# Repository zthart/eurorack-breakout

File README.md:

# Eurorack Power Breakout

**Warning**: I am, perhaps, the furthest thing there is from an EE or CE. 
I have a rudimentary (at best) understanding of the physics involved in the electronics.
I mostly understand the following:

1. Give black rectangles too much power and \*pop\*.
2. Give spicy cylinders too much power and \*pop\*.
3. Send power the wrong way and something very expensive goes \*pop\*.
4. \*pop\* is bad.

The `eurorack_breakout` directory contains the KiCad project, schematic, and pcb files for this project.

The first prototypes of the `norev` boards have performed well at what they're meant to do, and a new batch of the boards has been ordered with a few improvements (reverse-polarity protection diodes for the rack supply +12/-12/+5V rails, primarily).
I have some extras of both the `norev` and `rev0.3` boards, and would be happy to send you one if you reach out and cover shipping.

## Oops! All SMD

You'll notice everything is a SMD component, aside from the pin headers on either end of the PCB.
None of the package sizes are _too_ too difficult, so I'm confident you'll figure it out.
The two ceramic decoupling capacitors on the linear regulators (`C3` and `C6`), as well as the reverse polarity diodes (`D1-D3`) are the smallest packages, and may be tricky.
Just be patient use tweezers, flux, and make sure your soldering iron is tinned and you're using a relatively-small-ish conical tip.
I used the hand-soldering extended footprints KiCad provides for each package when possible, so every component should have enough room to get a soldering iron around.

## Optional Regulated Power

As is, the board (when populated with only the reverse-polarity protection diodes) can be used to route 10- or 16-pin Eurorack power from a 2-by connector to a 1-by connector with one less ground. 
The Gate and CV lines on the 16-pin connector are also not routed anywhere (except between columns).
If you need these lines my recommendation is to simply not need them (I don't need them for my purposes so I decided not to route them, I don't know how many modules actually use them).
There are two solder jumpers on the board -- `JP1` and `JP2` -- to pass +12V from the Eurorack power through the LM1117-3.3 and LM1117-5.0 circuits, respectively.
If you're using 5V tolerant digital circuitry in your module and want to support just 16-pin connectors, you don't even need to populate the board (sans diodes - those need to be populated for anything but ground be connected).

### Messing up

If you mess up, both halves of the circuit are identical (sans ferrite bead).
The silkscreen will be wrong, but there's not much stopping you from using the 3V3 side as the 5V side or vice-versa.
This might be helpful if you make a mistake while soldering.
If you have soldered some components on successfully before your mistake, I'd recommend cutting the jumper trace that corresponds to the circuit on which you've made your mistake.

### 3V3 Circuit

The 3.3V circuit consists of the following:

|Part Ref|Value|Type|
|:-:|--:|--:|
|`U1`|LM1117-3.3|Linear Regulator|
|`C1`|47uF|Aluminum Polymer Cap|
|`C2`|47uF|Aluminum Polymer Cap|
|`C3`|0.1uF|Ceramic Cap|
|`FB1`\*| -- |Ferrite Bead|

_\*The ferrite bead is not needed if you don't want/need a slightly cleaner 3.3V supply._
_The circuit will work without it populated, but pin 7 on the breakout-side connector will be NC. You can bridge the FB footprint, or pin 7 and 8 on the breakout-side connector directly if you would like 2 3V3 pins._

If you don't need 3.3V power for your testing, cut the trace connecting the two halves of the jumper with a razor blade or hobby knife (carefully).
You can also not cut it, and just leave the entire portion of the board unpopulated.
Note that the Aluminum caps are polarized - the footprints and packaging should make it clear which side is which. 
All 4 caps have the same orientation.

### 5V Circuit

The 5V circuit consists of the following:

|Part Ref|Value|Type|
|:-:|--:|--:|
|`U2`|LM1117-5.0|Linear Regulator|
|`C4`|47uF|Aluminum Polymer Cap|
|`C5`|47uF|Aluminum Polymer Cap|
|`C6`|0.1uf|Ceramic Cap|

If you don't need 5V power for your testing, cut the trace connecting the two halves of the jumper with a razor blade or hobby knife (carefully).
The same applies to the 3V3 circuit - you can choose to not cut it as well. 
If the circuit is unpopulated nothing will change.
I would personally recommend cutting it only in the case that you mess up one half of it and still want to use the other.

## BOM

|Part Ref|Value|Type|Link|
|:-:|--:|--:|:-:|
|`C1`, `C2`, `C4`, `C5`|47uF|Aluminum Polymer Cap|([digikey](https://www.digikey.com/en/products/detail/kemet/A768EB476M1VLAE042/13420538))|
|`C3`, `C6`|0.1uF|Ceramic Cap|([digikey](https://www.digikey.com/en/products/detail/w-rth-elektronik/885012208087/5454754))|
|`U1`|LM1117-3.3\*|Linear Regulator|([digikey](https://www.digikey.com/en/products/detail/on-semiconductor/LM1117MPX-33NOPB/13559953))|
|`U2`|LM1117-5.0\*|Linear Regulator|([digikey](https://www.digikey.com/en/products/detail/on-semiconductor/LM1117MPX-50NOPB/13559966))|
|`FB1`| -- |Ferrite Bead|([digikey](https://www.digikey.com/en/products/detail/w-rth-elektronik/742792312/1639577))|
|`D1-D3`|1N5819\*\*|Schottky Diode|([digikey](https://www.digikey.com/en/products/detail/diodes-incorporated/1N5819HW-7-F/814970))

_\*I bought these very cheaply._
_Notice that they're from ON Semiconductor rather than the more expensive LM1117-series from TI._
_As best I could tell, the principal difference is a slightly lower rejection ratio of 65dB, whereas the TI models report a PSRR of 75dB._
_My presumption here is that, while you can power your dev board/prototypes from your rack while it's fully on, you might want to have a test Eurorack supply for doing this dev work._
_Better yet, a benchtop supply (a Eurorack case w/ supply and a reasonble hobbyist benchtop supply run you about the same $$$, so I bought a case first)._
_This board might be slightly noisier with the ON Semiconductor regulators, but they're footprint compatible with the TI models if you are really worried about noise from the switching supply on your rack._

_\*\*I bought a few hundred of these a long time ago on `<insert Chinese Amazon here>` for another project, and used them here because I had them lying around._
_As of writing this, they're unavailable in the appropriate footprint on Digikey, but I imagine that they can be had on `<Chinese Amazon>` still - you may also find them on other electronic component supply shops._
_I won't link to a specific listing, since I prefer to source parts from places like Mouser or Digikey these days, but these can be had for about $1/lot of 100, if you're willing to wait a month or so for them to arrive in the mail `:^ )`_

## Board revision history

A quick rundown of the revision history of the board, mostly for my own sanity. 
Note that I'm tracking the schematic revision and board revision numbers separately. 
The schematic may be unchanged between board revisions.

### `norev`

My first boards were sent off to the fab without a revision marked on them because it was like 2AM when I uploaded them.
These boards have the wrong license shorthand on the silkscreen, and no test points.

### `rev01`

The `rev01` boards were the boards first uploaded to github with the correct CC license on the silkscreen, along with a revision number.
Front-side test points were added for the 3V3 and 5V traces.
I have not sent this board revision to be fabbed.

### `rev02`

The `rev02` boards differ from the previous revisions as follows:

- +12V and -12V lines are 0.4mm think, rather than 0.25mm as on previous revisions
- The info silkscreen in the top right hand corner was change to remove the line about the optional regulators - too much text
- The length of the board was reduced by 25 mils (should reduce the cost of the board a tiny amount)
- More vias were added to the copper pours used for heat dissipation for the linear regulators
- The positions of `C2` and `C3` were swapped, so that all **odd-numbered** components are on the upper half of the front of the board, and all **even-numbered** components are on the lower half (this should hopefully make populating only the 3V3 or 5V regulator circuits a bit more clear, as you'll only be soldering one half of the board).

I have not sent this board revision to be fabbed.

### `rev0.3`

The `rev0.3` boards differ from the previous revisions as follows:

- Reverse-polarity protection diodes for the rack +12V, -12V, and +5V lines (I recommend 1N5819 diodes, any reasonably tolerant schottky diode should work). These have an SOD-123 footprint, and are somewhat tricky to hand solder.
- OSHW Silkscreen and new `zzzzzzzz` graphic on back silkscreen/mask.
- Various silkscreen adjustments to move some component references out from underneath others
- Pad jumpers for the 3v3 and 5v enable lines are incorporated into the schematic and labelled as `JP1` and `JP2` respectively.
- Capacitor reference values have changed. `C1-C3` are the two aluminum and ceramic decoupling capacitor for the 3v3 circuit. `C4-C6` are the two aluminum and ceramic decoupling capacitor for the 5v circuit.
- The project licence has been switched to the CERN-OHL-P v2 license, and the silkscreen updated accordingly.

A panel of these boards has been sent off to the fab.

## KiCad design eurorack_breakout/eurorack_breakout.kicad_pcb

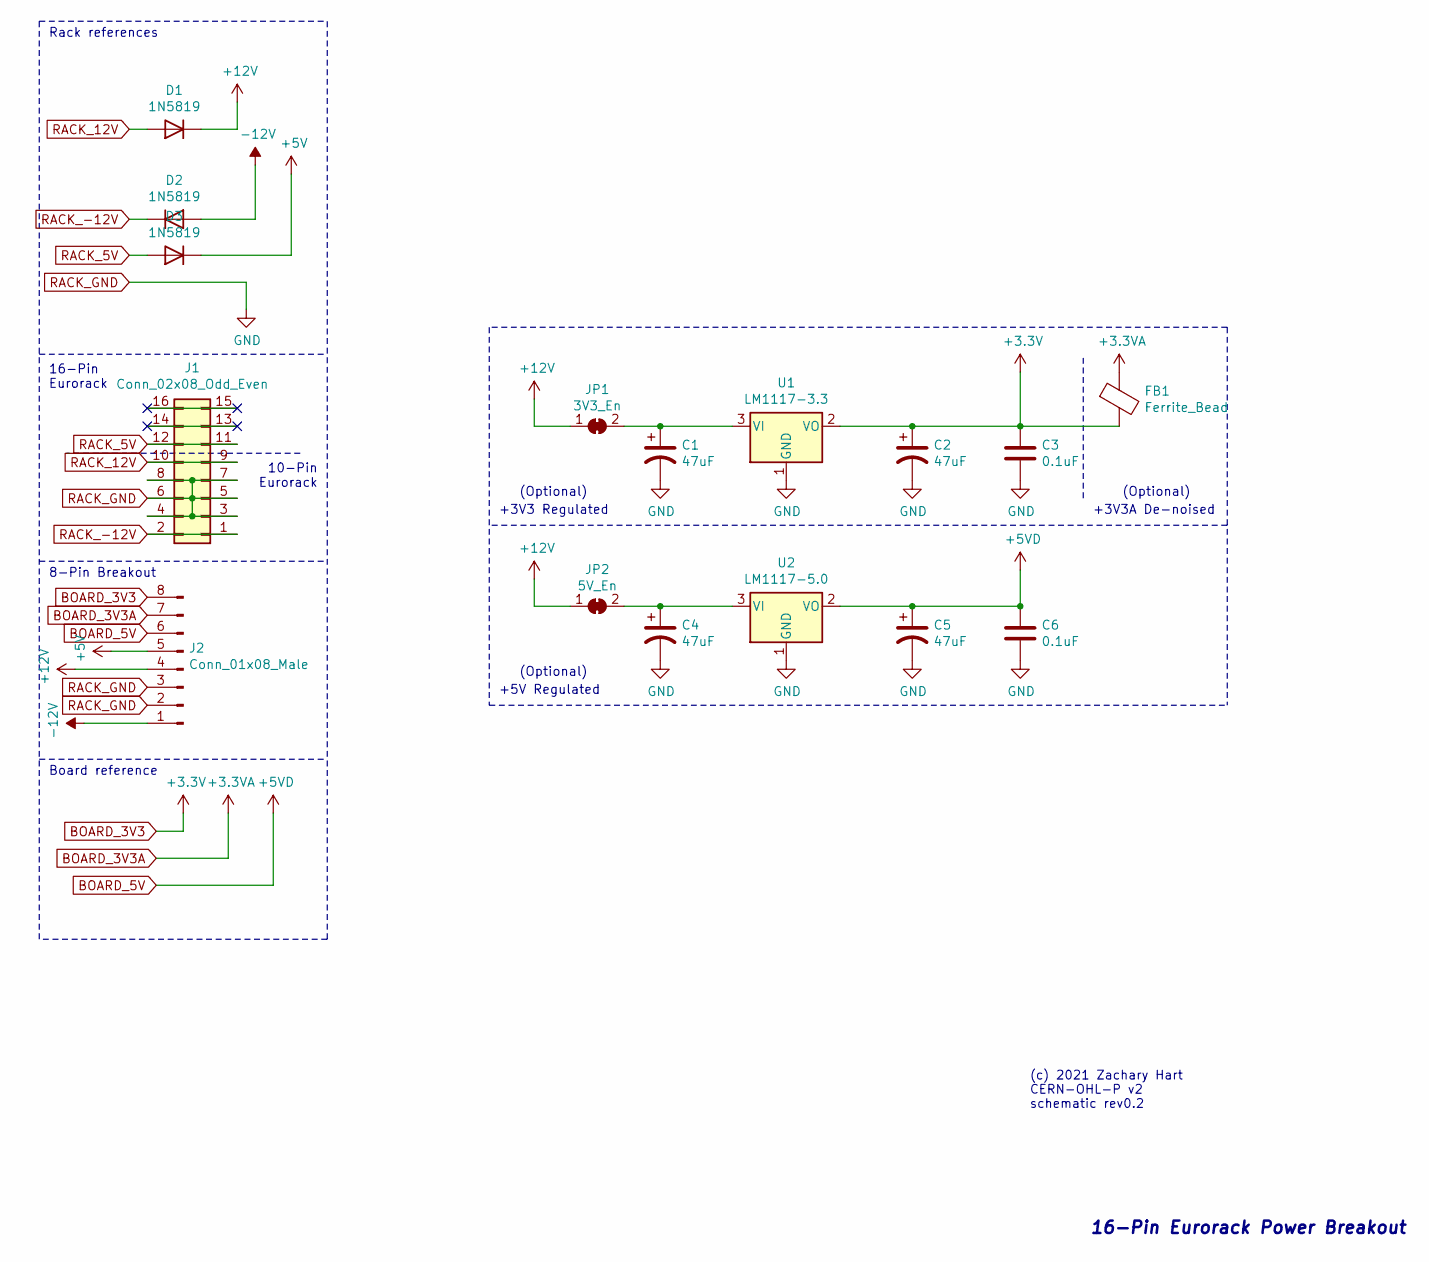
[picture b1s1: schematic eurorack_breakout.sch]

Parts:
C1, C2, C4, C5: 47uF; CP_Elec_6.3x5.7
C3, C6: 0.1uF; C_1206_3216Metric_Pad1.33x1.80mm_HandSolder
D1, D2, D3: 1N5819; D_SOD-123
FB1: Ferrite_Bead; L_1210_3225Metric_Pad1.42x2.65mm_HandSolder
J1: Conn_02x08_Odd_Even; PinHeader_2x08_P2.54mm_Vertical
J2: Conn_01x08_Male; PinHeader_1x08_P2.54mm_Vertical
JP1: 3V3_En; SolderJumper-2_P1.3mm_Bridged_RoundedPad1.0x1.5mm
JP2: 5V_En; SolderJumper-2_P1.3mm_Bridged_RoundedPad1.0x1.5mm
U1: LM1117-3.3; SOT-223-3_TabPin2
U2: LM1117-5.0; SOT-223-3_TabPin2

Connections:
+5V: D3.1 (K), J2.5
+12V: D1.1 (K), J2.4, JP1.1 (A), JP2.1 (A)
-12V: D2.2 (A), J2.1
BOARD_3V3: C2.1, C3.1, FB1.2, J2.8, U1.2 (VO); also elsewhere on the board
BOARD_3V3A: FB1.1, J2.7
BOARD_5V: C5.1, C6.1, J2.6, U2.2 (VO); also elsewhere on the board
unnamed: C1.1, JP1.2 (B), U1.3 (VI)
unnamed: C4.1, JP2.2 (B), U2.3 (VI)
unnamed: J1.13, J1.14
unnamed: J1.15, J1.16
RACK_5V: D3.2 (A), J1.11, J1.12
RACK_12V: D1.2 (A), J1.9, J1.10
RACK_-12V: D2.1 (K), J1.1, J1.2
RACK_GND: C1.2, C2.2, C3.2, C4.2, C5.2, C6.2, J1.3, J1.4, J1.5, J1.6, J1.7, J1.8, J2.2, J2.3, U1.1 (GND), U2.1 (GND)

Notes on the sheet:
Rack references
16-Pin Eurorack
8-Pin Breakout
Board reference
+5V Regulated
+3V3 Regulated
+3V3A De-noised
10-Pin Eurorack
(Optional)
16-Pin Eurorack Power Breakout
(c) 2021 Zachary Hart CERN-OHL-P v2 schematic rev0.2

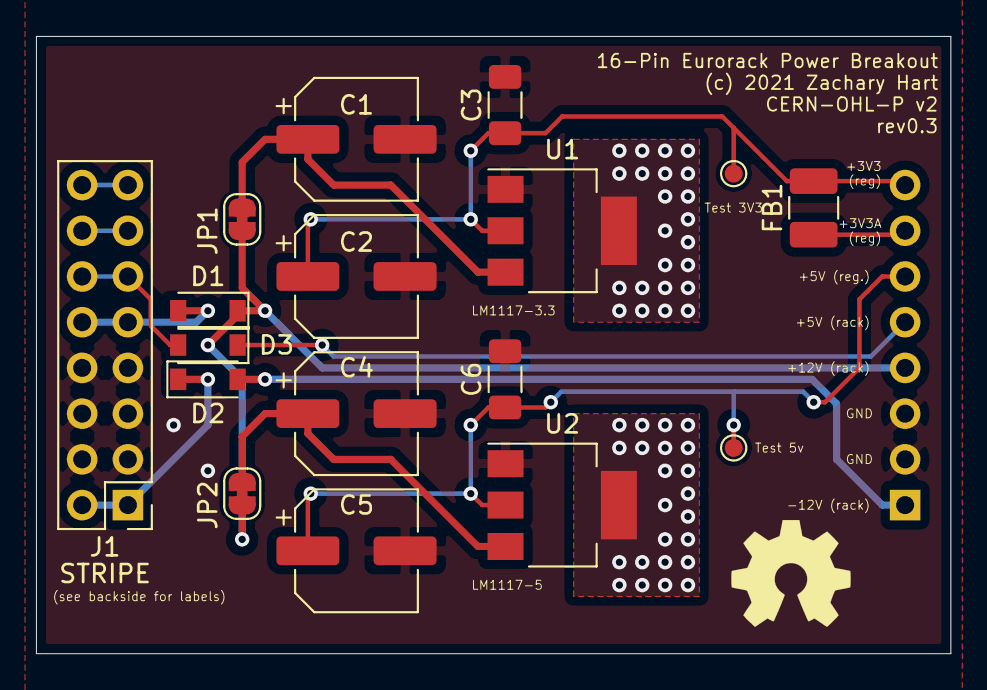
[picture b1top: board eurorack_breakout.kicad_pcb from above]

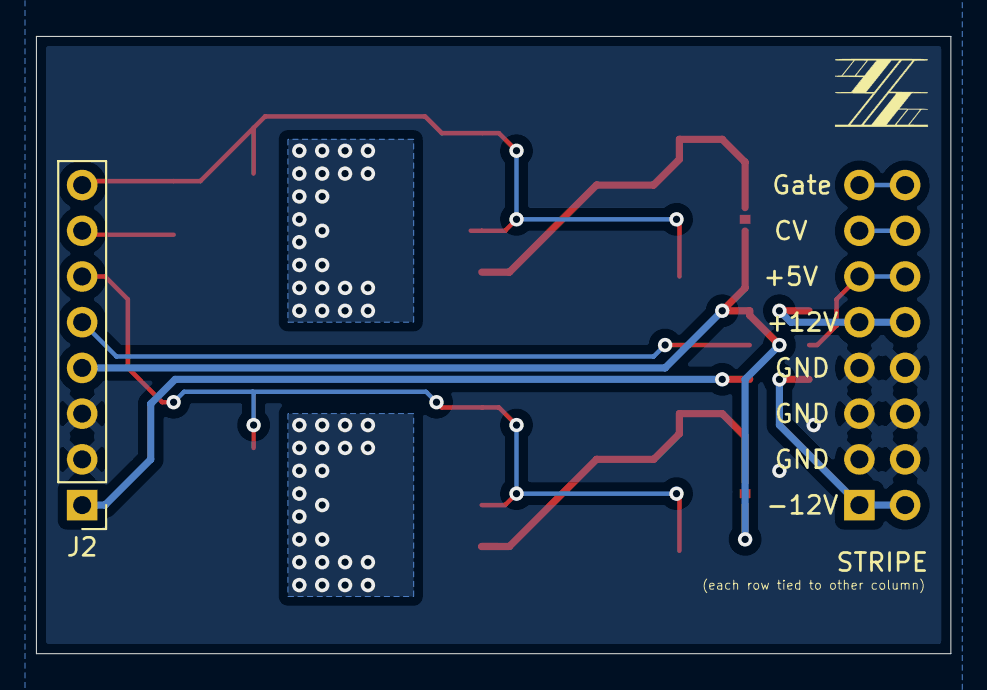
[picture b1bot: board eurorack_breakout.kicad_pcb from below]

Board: 2 copper layers, 50.8 x 34.3 mm, 19 parts (2 on the bottom side), 14 nets.

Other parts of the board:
Ref**: Val**; zzzzzzzz_new_5.2x3.75mm
Test 3V3, Test 5v: TestPoint_Pad_D1.0mm

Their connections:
BOARD_3V3: Test 3V3.1; also elsewhere on the board
BOARD_5V: Test 5v.1; also elsewhere on the board

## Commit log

2021-04-16 eh, different license
2021-04-16 test points for 3V3 and 5V on pcb
2021-04-16 board rev0.2
2021-04-17 goodbye miku :(
2021-04-17 flip breadboard-side silkscreen around
2021-05-22 Board rev0.3, new license, cleanup
    - Removed unneeded KiCad files
    - Updated license to CERN-OHL-P v2
    - Updated README
    - Project-level footprint library
2021-05-22 fix bad part value in README
